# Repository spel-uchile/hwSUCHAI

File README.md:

hwSUCHAI
========

PCB, antennas, 3D models, and other parts of the Cubesat SUCHAI.

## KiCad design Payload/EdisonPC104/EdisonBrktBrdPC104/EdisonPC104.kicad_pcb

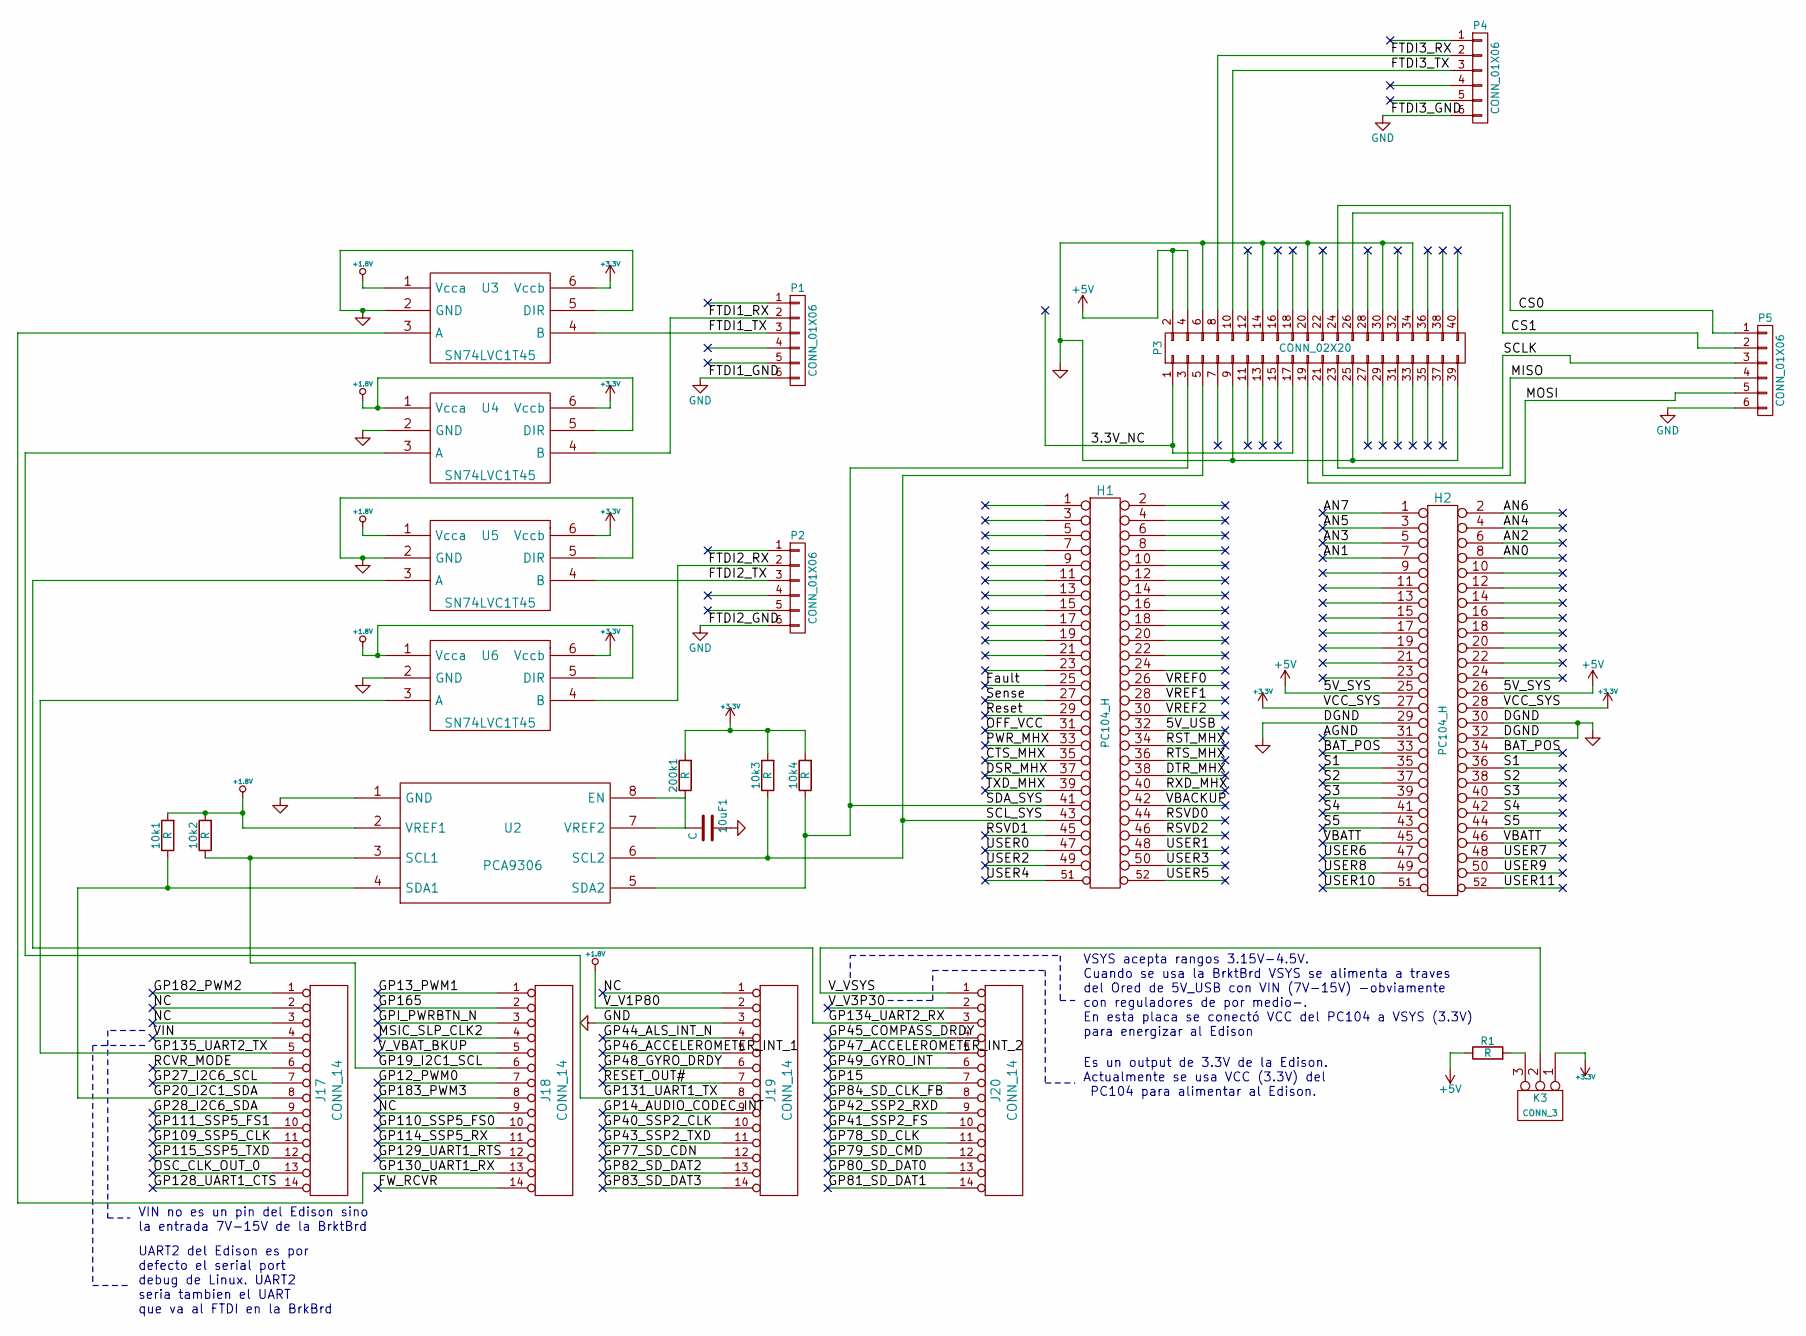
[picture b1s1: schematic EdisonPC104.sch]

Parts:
10k1, 10k2, 10k3, 10k4, 200k1: R; R_1206_HandSoldering
10uF1: C; SMD-1206_Pol
H1, H2: PC104_H; Pin_Header_Straight_2x26
J17, J18, J19, J20: CONN_14; Pin_Header_Straight_1x14
K3: CONN_3; Pin_Header_Straight_1x03
P1, P2, P4, P5: CONN_01X06; Pin_Header_Angled_1x06
P3: CONN_02X20; Pin_Header_Straight_2x20
R1: R; Resistor_Horizontal_RM15mm
U2: PCA9306; SOIC-8-N
U3, U4, U5, U6: SN74LVC1T45; SOT-23-6

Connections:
+1.8V: 10k1.2, 10k2.2, J19.2, U2.2 (VREF1), U3.1 (Vcca), U4.1 (Vcca), U4.5 (DIR), U5.1 (Vcca), U6.1 (Vcca), U6.5 (DIR)
+3V3: 10k3.2, 10k4.2, 200k1.2, H2.27, H2.28, K3.1, U3.6 (Vccb), U4.6 (Vccb), U5.6 (Vccb), U6.6 (Vccb)
+5V: H2.25, H2.26, P3.2, P3.4, R1.1
/3.3V_NC: P3.1, P3.17
/5V_USB: H1.32
/AGND: H2.31
/AN0: H2.8
/AN1: H2.7
/AN2: H2.6
/AN3: H2.5
/AN4: H2.4
/AN5: H2.3
/AN6: H2.2
/AN7: H2.1
/BAT_POS: H2.33, H2.34
/CS0: P3.24, P5.1
/CS1: P3.26, P5.2
/CTS_MHX: H1.35
/DSR_MHX: H1.37
/DTR_MHX: H1.38
/FTDI1_RX: P1.2, U4.4 (B)
/FTDI1_TX: P1.3, U3.4 (B)
/FTDI2_RX: P2.2, U6.4 (B)
/FTDI2_TX: P2.3, U5.4 (B)
/FTDI3_RX: P3.8, P4.2
/FTDI3_TX: P3.10, P4.3
/FW_RCVR: J18.14
/Fault: H1.25
/GP12_PWM0: J18.7
/GP13_PWM1: J18.1
/GP14_AUDIO_CODEC_INT: J19.9
/GP15: J20.7
/GP19_I2C1_SCL: 10k2.1, J18.6, U2.3 (SCL1)
/GP20_I2C1_SDA: 10k1.1, J17.8, U2.4 (SDA1)
/GP27_I2C6_SCL: J17.7
/GP28_I2C6_SDA: J17.9
/GP40_SSP2_CLK: J19.10
/GP41_SSP2_FS: J20.10
/GP42_SSP2_RXD: J20.9
/GP43_SSP2_TXD: J19.11
/GP44_ALS_INT_N: J19.4
/GP45_COMPASS_DRDY: J20.4
/GP46_ACCELEROMETER_INT_1: J19.5
/GP47_ACCELEROMETER_INT_2: J20.5
/GP48_GYRO_DRDY: J19.6
/GP49_GYRO_INT: J20.6
/GP77_SD_CDN: J19.12
/GP78_SD_CLK: J20.11
/GP79_SD_CMD: J20.12
/GP80_SD_DAT0: J20.13
/GP81_SD_DAT1: J20.14
/GP82_SD_DAT2: J19.13
/GP83_SD_DAT3: J19.14
/GP84_SD_CLK_FB: J20.8
/GP109_SSP5_CLK: J17.11
/GP110_SSP5_FS0: J18.10
/GP111_SSP5_FS1: J17.10
/GP114_SSP5_RX: J18.11
/GP115_SSP5_TXD: J17.12
/GP128_UART1_CTS: J17.14
/GP129_UART1_RTS: J18.12
/GP130_UART1_RX: J18.13, U3.3 (A)
/GP131_UART1_TX: J19.8, U4.3 (A)
/GP134_UART2_RX: J20.3, U5.3 (A)
/GP135_UART2_TX: J17.5, U6.3 (A)
/GP165: J18.2
/GP182_PWM2: J17.1
/GP183_PWM3: J18.8
/GPI_PWRBTN_N: J18.3
/MISO: P3.21, P5.4
/MOSI: P3.19, P5.5
/MSIC_SLP_CLK2: J18.4
/NC: J17.2, J17.3, J18.9, J19.1
/OFF_VCC: H1.31
/OSC_CLK_OUT_0: J17.13
/PWR_MHX: H1.33
/RCVR_MODE: J17.6
/RESET_OUT#: J19.7
/RST_MHX: H1.34
/RSVD0: H1.44
/RSVD1: H1.45
/RSVD2: H1.46
/RTS_MHX: H1.36
/RXD_MHX: H1.40
/Reset: H1.29
/S1: H2.35, H2.36
/S2: H2.37, H2.38
/S3: H2.39, H2.40
/S4: H2.41, H2.42
/S5: H2.43, H2.44
/SCLK: P3.23, P5.3
/SCL_SYS: 10k3.1, H1.43, P3.5, U2.6 (SCL2)
/SDA_SYS: 10k4.1, H1.41, P3.3, U2.5 (SDA2)
/Sense: H1.27
/TXD_MHX: H1.39
/USER0: H1.47
/USER1: H1.48
/USER2: H1.49
/USER3: H1.50
/USER4: H1.51
/USER5: H1.52
/USER6: H2.47
/USER7: H2.48
/USER8: H2.49
/USER9: H2.50
/USER10: H2.51
/USER11: H2.52
/VBACKUP: H1.42
/VBATT: H2.45, H2.46
/VIN: J17.4
/VREF0: H1.26
/VREF1: H1.28
/VREF2: H1.30
/V_V3P30: J20.2
/V_VBAT_BKUP: J18.5
/V_VSYS: J20.1, K3.2 (PM)
GND: 10uF1.1, H2.29, H2.30, H2.32, J19.3, P1.6, P2.6, P3.6, P3.9, P3.14, P3.20, P3.25, P3.30, P3.34, P3.39, P4.6, P5.6, U2.1 (GND), U3.2 (GND), U3.5 (DIR), U4.2 (GND), U5.2 (GND), U5.5 (DIR), U6.2 (GND)
unnamed: 10uF1.2, 200k1.1, U2.7 (VREF2), U2.8 (EN)
unnamed: K3.3, R1.2

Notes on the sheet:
VSYS acepta rangos 3.15V-4.5V. Cuando se usa la BrktBrd VSYS se alimenta a traves del Ored de 5V_USB con VIN (7V-15V) -obviamente con reguladores de por medio-. En esta placa se conectó VCC del PC104 a VSYS (3.3V) para energizar al Edison
UART2 del Edison es por defecto el serial port debug de Linux. UART2 seria tambien el UART que va al FTDI en la BrkBrd
Es un output de 3.3V de la Edison. Actualmente se usa VCC (3.3V) del PC104 para alimentar al Edison.
VIN no es un pin del Edison sino la entrada 7V-15V de la BrktBrd

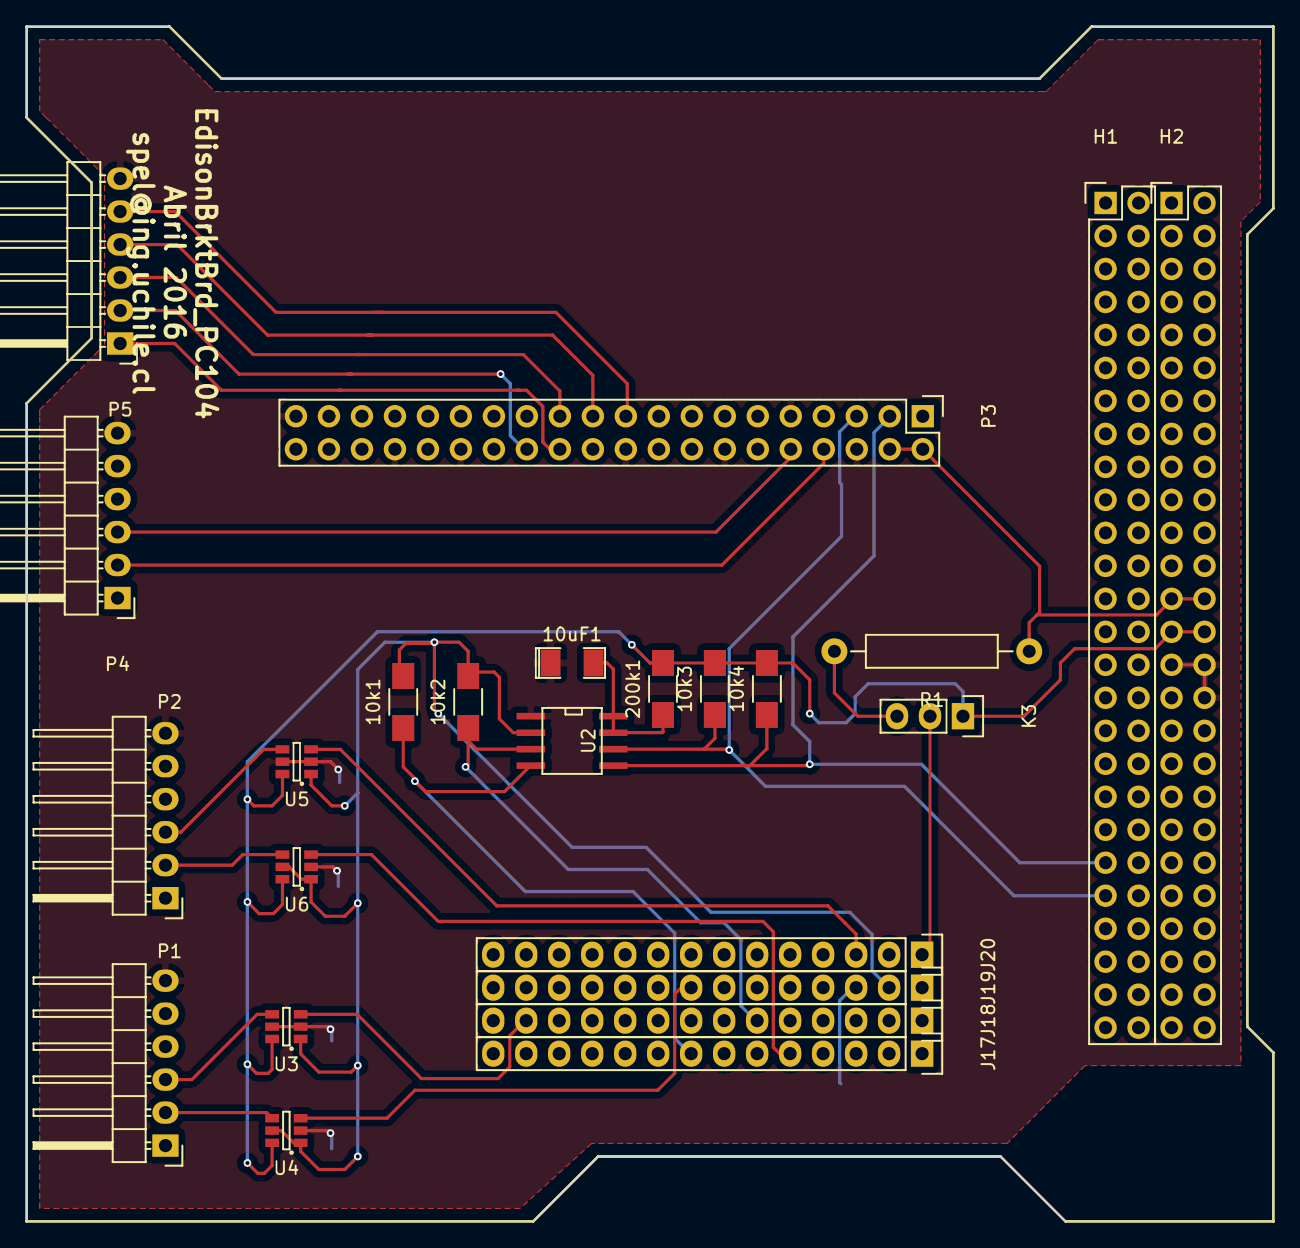
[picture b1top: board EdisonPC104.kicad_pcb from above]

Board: 2 copper layers, 96.0 x 92.0 mm, 24 parts (0 on the bottom side), 35 nets.

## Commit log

2014-07-28 se suben archivos de Alex, que contienen los modelos de las placas de antenas (despliegue y balun) y las de el payload (camara-langmuir)
2014-07-28 correcion del ingles
2014-08-18 se agraga doc CDS
2014-08-18 agrego archivo
2014-08-26 se agrega cad del suchai
2014-08-26 se actualizan PARTLIST de placa antenas, balun y payload. Faltan aprox 25% de componentes
2014-08-29 se modifican las placas: antena (acomodar switch en otro lugar y rotar resistencia para mejor amarre, se crea v7 con las modif y v6b sin cambios, se crean gerber), balun (se crean gerber), payload (s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
2014-10-08 se actualizan listas de partes
2015-04-09 se generan versiones para PCB de adaptacion Edison PC104
2015-08-10 se agrega piezas pequeñas de lanzador de langmuir probe
2015-10-08 se agregan datasheet para usarlos de fuene de info para el CAD del SUCHAI
2016-04-01 se crea nueva version de placa para alojar Rasp Zero y Edison. Se parte con arreglar los errores detectados en la parte de Edison
2016-04-07 se corrige bug de ruteo de UART1 y 2
2016-04-11 se declara lista la mita Edison de la placa
2016-04-26 se agrega rapberry zero al PCB
